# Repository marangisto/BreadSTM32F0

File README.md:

# BreadSTM32F0
Breadboard breakout for STM32F0

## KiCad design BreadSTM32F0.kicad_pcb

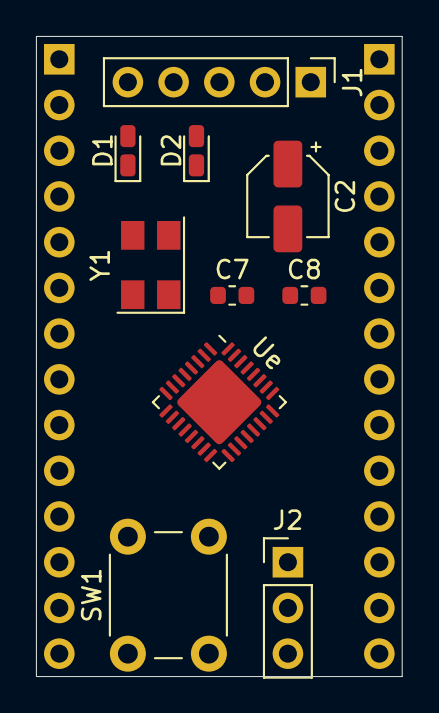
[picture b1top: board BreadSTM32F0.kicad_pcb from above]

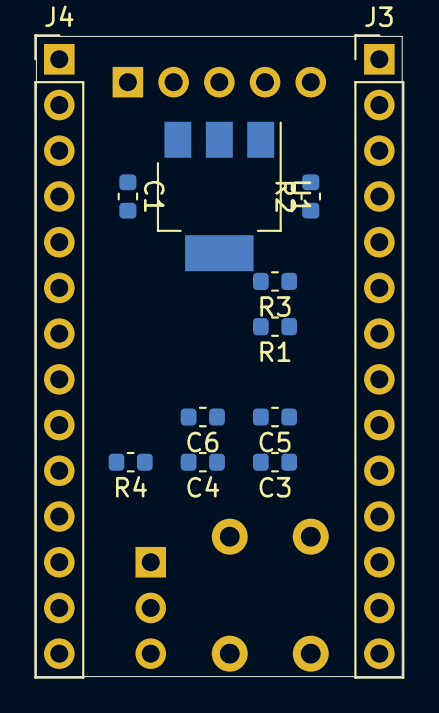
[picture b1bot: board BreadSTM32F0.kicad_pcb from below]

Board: 2 copper layers, 20.3 x 35.6 mm, 22 parts (12 on the bottom side), 36 nets, no tracks yet.

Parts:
C1, C3, C5, C6: 100n; C_0603_1608Metric
C2: 10u; CP_Elec_4x5.8
C4: 10n; C_0603_1608Metric
C7, C8: 27p; C_0603_1608Metric
D1, D2: LED; LED_0603_1608Metric_Castellated
J1: SWD; PinHeader_1x05_P2.54mm_Vertical
J2: Conn_01x03_Male; PinHeader_1x03_P2.54mm_Vertical
J3, J4: Conn_01x14_Male; PinHeader_1x14_P2.54mm_Vertical
R1, R2: 330; R_0603_1608Metric
R3: 10k; R_0603_1608Metric
R4: 470; R_0603_1608Metric
SW1: SW_Push; SW_PUSH_6mm
U1: LD1117S33TR_SOT223; SOT-223-3_TabPin2
Ue: STM32F051K8Ux; QFN-32-1EP_5x5mm_P0.5mm_EP3.45x3.45mm
Y1: 8MHz; Crystal_SMD_5032-4Pin_5.0x3.2mm

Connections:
3V3: C2.1, C4.1, C5.1, C6.1, J1.1, J2.1, J3.1, J4.3, R1.1, U1.2, Ue.1, Ue.5, Ue.17
GND: C1.2, C2.2, C3.2, C4.2, C5.2, C6.2, C7.2, C8.2, D1.1, D2.1, J1.3, J2.3, J3.2, J4.2, SW1.1, U1.1, Ue.33, Y1.2, Y1.4
unnamed: C7.1, Ue.2, Y1.1
unnamed: C8.1, R4.2, Y1.3
unnamed: D1.2, R1.2
unnamed: D2.2, R2.2
unnamed: J2.2, R3.2
unnamed: R3.1, Ue.31
unnamed: R4.1, Ue.3
PA0: J3.3, Ue.6
PA1: J3.4, Ue.7
PA2: J3.5, Ue.8
PA3: J3.6, Ue.9
PA4: J3.7, Ue.10
PA5: J3.8, Ue.11
PA6: J3.9, Ue.12
PA7: J3.10, Ue.13
PA8: J3.14, Ue.18
PA9: J4.14, Ue.19
PA10: J4.13, Ue.20
PA11: J4.12, Ue.21
PA12: J4.11, Ue.22
PA15: J4.10, R2.1, Ue.25
PB0: J3.11, Ue.14
PB1: J3.12, Ue.15
PB2: J3.13, Ue.16
PB3: J4.9, Ue.26
PB4: J4.8, Ue.27
PB5: J4.7, Ue.28
PB6: J4.6, Ue.29
PB7: J4.5, Ue.30
PB8: J4.4, Ue.32
RESET: C3.1, J1.5, SW1.2, Ue.4
SWCLK: J1.2, Ue.24
SWDIO: J1.4, Ue.23
VIN: C1.1, J4.1, U1.3

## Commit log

2019-05-13 Initial schematic.
2019-05-13 Assigned footprints.
2019-05-15 Initial placement.
